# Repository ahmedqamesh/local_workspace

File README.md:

# MyWorkSpace includes a set of libraries and functions for analysis and plotting.
#

# Links
Geant4 :http://geant4.cern.ch/support/download.shtml
Attenuation Data: http://henke.lbl.gov/optical_constants/
http://physics.nist.gov/PhysRefData/XrayMassCoef/tab3.html (only mass absorption coeff Low range)
http://physics.nist.gov/cgi-bin/Xcom/xcom3_1
http://physics.nist.gov/PhysRefData/Xcom/html/xcom1.html  (mass abs coeff  with photoeffekt, compton usw..)	
https://physics.nist.gov/PhysRefData/XrayTrans/Html/search.html			 (X-ray transition energies by element(s), transition(s), and/or energy/wavelength range. )  
# Need to install 
pip install lmfit

# Geant4 installation
wget http://geant4.cern.ch/support/source/geant4.10.01.p01.tar.gz
cmake -DGEANT4_USE_GDML=ON -DGEANT4_INSTALL_DATA=ON -DGEANT4_USE_G3TOG4=ON -DGEANT4_USE_OPENGL_X11=ON -DCMAKE_INSTALL_PREFIX=/home/silab62/HEP/geant4.10.01-install -DGEANT4_BUILD_MULTITHREADED=ON -DGEANT4_USE_QT=ON -DCLHEP_ROOT_DIR=/home/silab62/HEP/Tools/clhep/install ../geant4.10.01.p01
make -j
make install
source /home/silab62/HEP/geant4-install/bin/geant4.sh

# CLHEP installation  
mkdir Tools 
mkdir build install source
cd /home/silab62/HEP/Tools/clhep/build/
mkdir clhep-2.1.3.1
cd clhep-2.1.3.1
cmake ../../source/clhep/
ccmake .
#change CMAKE_INSTALL_PREFIX to /home/silab62/HEP/Tools/clhep/install/
make 
make install

# Root installation 
# First Some libraries:
sudo apt  install cmake
sudo apt-get install git dpkg-dev make g++ gcc binutils libx11-dev libxpm-dev libxft-dev libxext-dev 
sudo apt-get install build-essential git subversion
sudo apt-get install gfortran libssl-dev libpcre3-dev xlibmesa-glu-dev libglew1.5-dev libftgl-dev libmysqlclient-dev libfftw3-dev 
sudo apt-get install libcfitsio-dev graphviz-dev libavahi-compat-libdnssd-dev libldap2-dev python-dev libxml2-dev libkrb5-dev libgsl0-dev libqt4-dev ccache
#Install font packages:
sudo apt-get install xfsprogs #(xfs xfstt)
sudo apt-get install t1-xfree86-nonfree ttf-xfree86-nonfree ttf-xfree86-nonfree-syriac xfonts-75dpi xfonts-100dpi
#Download root itself
Go to https://root.cern.ch/content/release-61804
or 
The entire ROOT source can be obtained from our public Git repository:
git clone http://github.com/root-project/root.git
#The release specific tag can be obtained using:
cd root
git checkout -b v6-18-04 v6-18-04
## Building
Make a directory for building
    $ mkdir build
    $ cd build

Run cmake and make

    $ cmake ../root
    $ make -j8
    $ sudo make install

Setup and run ROOT
    $ source bin/thisroot.sh
    $ root
    
nano ~/.bashrc
#Add the line
source ~/bin/thisroot.sh #/home/qamesh/Installations/root_installer/Source/build/bin/thisroot.sh
export PATH=$ROOTSYS/bin:$PATH
export LD_LIBRARY_PATH=$ROOTSYS/lib:$LD_LIBRARY_PATH   

Add the following in Eclipse
Go to Preferences → C/C++ → Build → Environment.
Add $ROOTSYS variable and its value.
Add $PATH variable. Eclipse needs this path because it will run gdb and our Makefile, which involves executing root-config and rootcling.
Add $DYLD_LIBRARY_PATH on macOS or $LD_LIBRARY_PATH on Linux. When running the project Eclipse needs to know where ROOT’s shared libraries are located.

these two you have to set

the /home/patrick/root/lib has to be also in the libraries
you have to go to PyDeV -> Interpreters -> python interpreter
and there you have to set /home/patrick/root/lib in libraries
and LD_LIBRARY_PATH & ROOTSYS in environment

./configure --all --prefix=/home/silab62/HEP/Tools/root6/install
https://root-forum.cern.ch/t/using-root-gui-in-eclipse/30581

#For Ubuntu 14.04 run: sudo mkdir /usr/include/freetype && sudo cp /usr/include/freetype2/freetype.h /usr/include/freetype/freetype.h
To unistall 
sudo apt-get remove root-system-bin
sudo apt-get remove --auto-remove root-system-bin

# Install wine to run windows applications on Ubuntu
sudo apt install wine64
sudo apt install wine-development
sudo apt install wine-stable

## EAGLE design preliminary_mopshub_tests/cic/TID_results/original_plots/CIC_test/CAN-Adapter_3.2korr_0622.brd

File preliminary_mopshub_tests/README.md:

# Preliminary tests
The testing and validation of the MOPS-Hub includes strict assessments of its hardware components. This scripts involved in this repo aims to ensure the reliability,
functionality, and performance of the MOPS-Hub crate across various scenarios. 
An Arduino-based setup was built to test the modules under controlled conditions.

## List of scripts 
### Test Files
1. **test_can_interface_card.py**: Runs automated tests on the CAN Interface Card (CIC) to ensure correct operation. Data is collected continuously over an extended period using the Arduino-based setup.
2. **test_power_card.py**: Runs automated tests to validate the PP3-power card’s performance and functionality.
- Data is collected continuously over an extended period using the Arduino-based setup. 
- The script control over the connected power supply during operation.
3. **test_power_supply.py** : Controls the supply power during operation [Used during the Proton Campaign].

### Analysis Files
1. **analyze_cic_v2_results.py**: Processes and analyzes data from CAN Interface Card (CIC) tests including:
	- Total Ionizing Dose (TID).
	- Neutron Fluence.
	- Magnetic Field.
2. **analyze_cic_configurations_test.py**: to analyze the data of the VCAN voltages on the CAN Interface Card (CIC) under different Configurations.
3. **analyze_powersupply_results.py**: Analyzes the performance of the power supply to reflect current and voltage behavior of the connected DUT (Device Under Test).
4. **analyze_powercard_results.py**: Processes and analyzes data from PP3-power card tests including: 
	- Total Ionizing Dose (TID).
	- Neutron Fluence.
	- Magnetic Field.
5. **analyze_magnetic_field_results.py**: Creat a magnetic field map for the Lab setup.<br>

**Note**: Data from each test is saved in the directory: `$PROJ_HOME/preliminary_tests/output_dir/`

# Documentation
- Construction of MOPS-Hub document: [AT2-IP-EP-0021](https://edms.cern.ch/document/2600650/1).
- QA/QC of MOPS-Hub document: [AT2-IP-QA-0053](https://edms.cern.ch/document/2600650/1).

# Contributing and Contact Information:
We welcome contributions from the community please contact : 
- Felix Nitz : `fnitz@uni-wuppertal.de`.
- Ahmed Qamesh `ahmed.qamesh@cern.ch`.

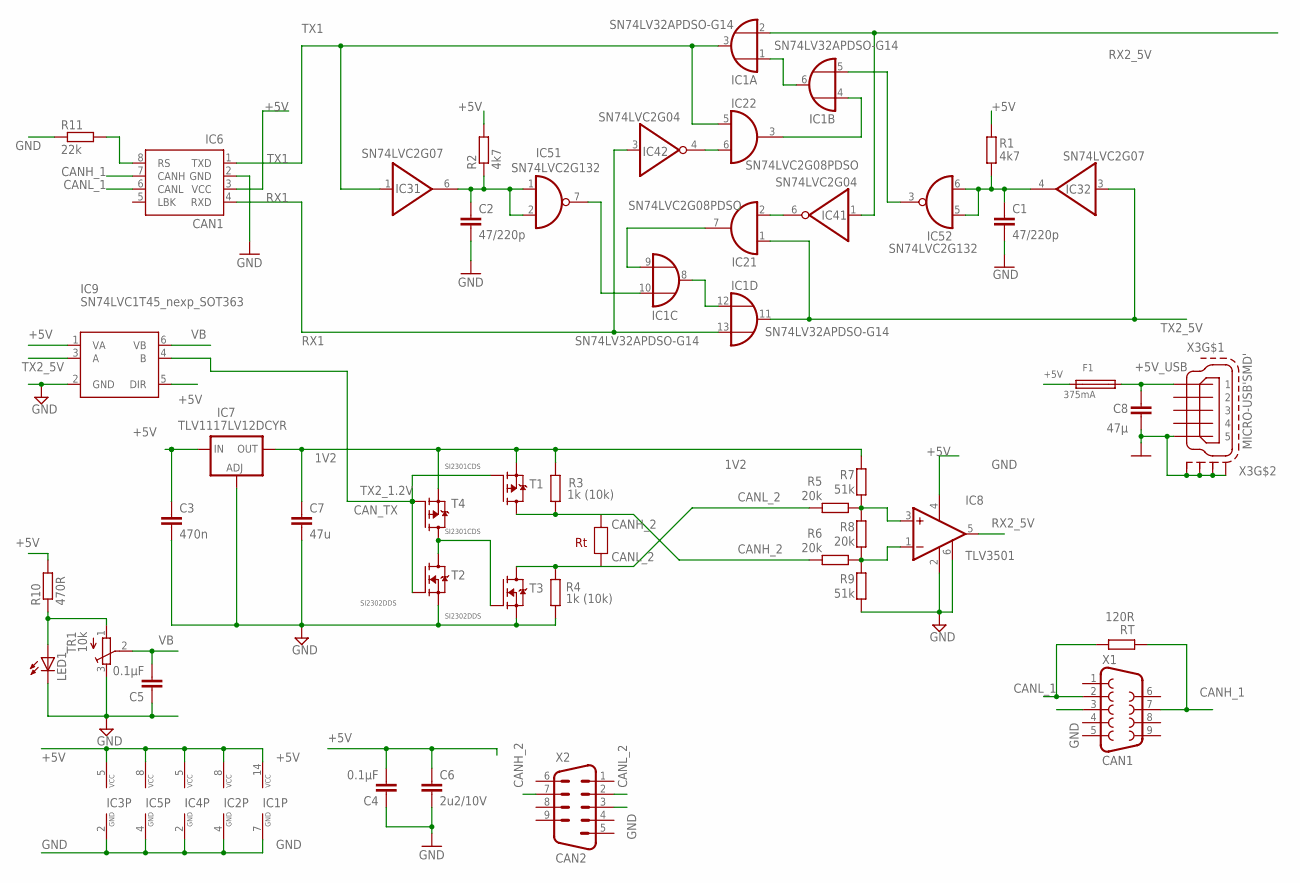
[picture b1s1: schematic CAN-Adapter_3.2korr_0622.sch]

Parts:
C1, C2: 47/220p; C0603
C3: 470n; C1206S
C4, C5: 0.1µF; C0805
C6: 2u2/10V; C0805
C7: 47u; C1206K
C8: 47µ; C1206K
F1: 375mA; 1206
IC1: SN74LV32APDSO-G14; PW_R-PDSO-G14
IC2: SN74LVC2G08PDSO; R-PDSO-G08_DCT
IC3: SN74LVC2G07; R-PDSO-G06
IC4: SN74LVC2G04; R-PDSO-G06
IC5: SN74LVC2G132; S-PDSO-G08_DCU
IC6: CAN1; SO-08
IC7: TLV1117LV12DCYR; SOT223
IC8: TLV3501; SOT23-6
IC9: SN74LVC1T45_nexp_SOT363; SOT363
LED1: LED3MM
R1, R2: 4k7; R0603
R3, R4: 1k (10k); R0603
R5, R6, R8: 20k; R0603
R7, R9: 51k; R0603
R10: 470R; R0603
R11: 22k; R0603
RT: 120R; R0603
T1, T4: SI2301CDS; SOT23
T2, T3: SI2302DDS; SOT23
TR1: 10k; TC33X-2
X1: CAN1; F09D
X2: CAN2; M09D
X3: MICRO-USB'SMD'; MICRO-USB_SMD

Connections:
1V2: C7.1, IC7.4 (OUT), R3.2, R7.1, T1.2 (S), T4.2 (S)
+5V: C3.1, C4.2, C6.1, F1.P$1 (1), IC1.14 (VCC), IC2.8 (VCC), IC3.5 (VCC), IC4.5 (VCC), IC5.8 (VCC), IC6.3 (VCC), IC7.3 (IN), IC8.4 (V+), IC9.1 (VA), IC9.5 (DIR), R1.2, R2.2, R10.2
+5V_USB: C8.1, F1.P$2 (2), X3.P$1 (1)
CANH_1: IC6.7 (CANH), RT.1, X1.7
CANH_2: R3.1, R6.1, T1.3 (D), X2.7
CANL_1: IC6.6 (CANL), RT.2, X1.2
CANL_2: R4.2, R5.1, T3.3 (D), X2.2
GND: C1.2, C2.2, C3.2, C4.1, C5.1, C6.2, C7.2, C8.2, IC1.7 (GND), IC2.4 (GND), IC3.2 (GND), IC4.2 (GND), IC5.4 (GND), IC6.2 (GND), IC7.1 (ADJ), IC8.2 (V-), IC8.6 (SHDN), IC9.2 (GND), LED1.K (C), R4.1, R9.2, R11.1, T2.2 (S), T3.2 (S), TR1.3 (E), X1.3, X2.3, X3.P$5 (5), X3.P$6 (S1), X3.P$7 (S2), X3.P$8 (S3), X3.P$9 (S4)
IC1,6: IC1.1 (I0), IC1.6 (O)
IC1,8: IC1.8 (O), IC1.12 (I0)
IC2,3: IC1.4 (I0), IC2.3 (Y)
IC2,7: IC1.9 (I0), IC2.7 (Y)
IC3,4: C1.1, IC3.4 (Y), IC5.5 (A), IC5.6 (B), R1.1
IC3,6: C2.1, IC3.6 (Y), IC5.1 (A), IC5.2 (B), R2.1
IC4,4: IC2.6 (B), IC4.4 (Y)
IC4,6: IC2.2 (B), IC4.6 (Y)
IC5,3: IC1.5 (I1), IC5.3 (Y)
IC5,7: IC1.10 (I1), IC5.7 (Y)
unnamed: T2.3 (D), T3.1 (G), T4.3 (D)
unnamed: LED1.A, R10.1, TR1.1 (A)
unnamed: IC6.8 (RS), R11.2
unnamed: IC8.3 (+IN), R5.2, R7.2, R8.1
unnamed: IC8.1 (-IN), R6.2, R8.2, R9.1
RX1: IC1.13 (I1), IC4.3 (A), IC6.4 (RXD)
RX2_5V: IC1.2 (I1), IC4.1 (A), IC8.5 (OUT)
TX1: IC1.3 (O), IC2.5 (A), IC3.1 (A), IC6.1 (TXD)
TX2_1.2V: IC9.4 (B), T1.1 (G), T2.1 (G), T4.1 (G)
TX2_5V: IC1.11 (O), IC2.1 (A), IC3.3 (A), IC9.3 (A)
VB: C5.2, IC9.6 (VB), TR1.2 (S)

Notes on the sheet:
CAN_TX
SN74LVC2G08PDSO

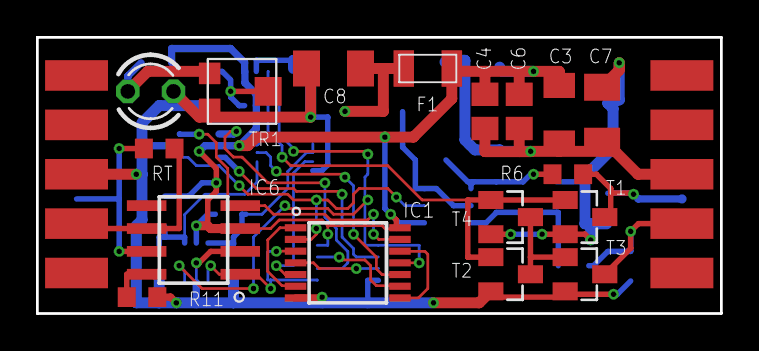
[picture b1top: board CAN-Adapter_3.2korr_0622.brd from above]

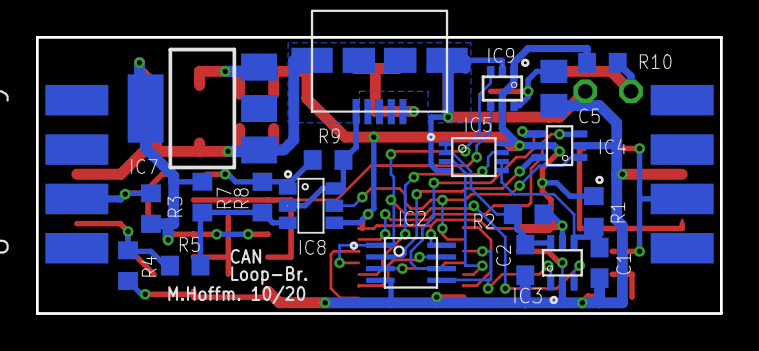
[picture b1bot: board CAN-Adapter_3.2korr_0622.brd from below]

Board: 2 copper layers, 38.0 x 15.3 mm, 39 parts (20 on the bottom side), 29 nets.

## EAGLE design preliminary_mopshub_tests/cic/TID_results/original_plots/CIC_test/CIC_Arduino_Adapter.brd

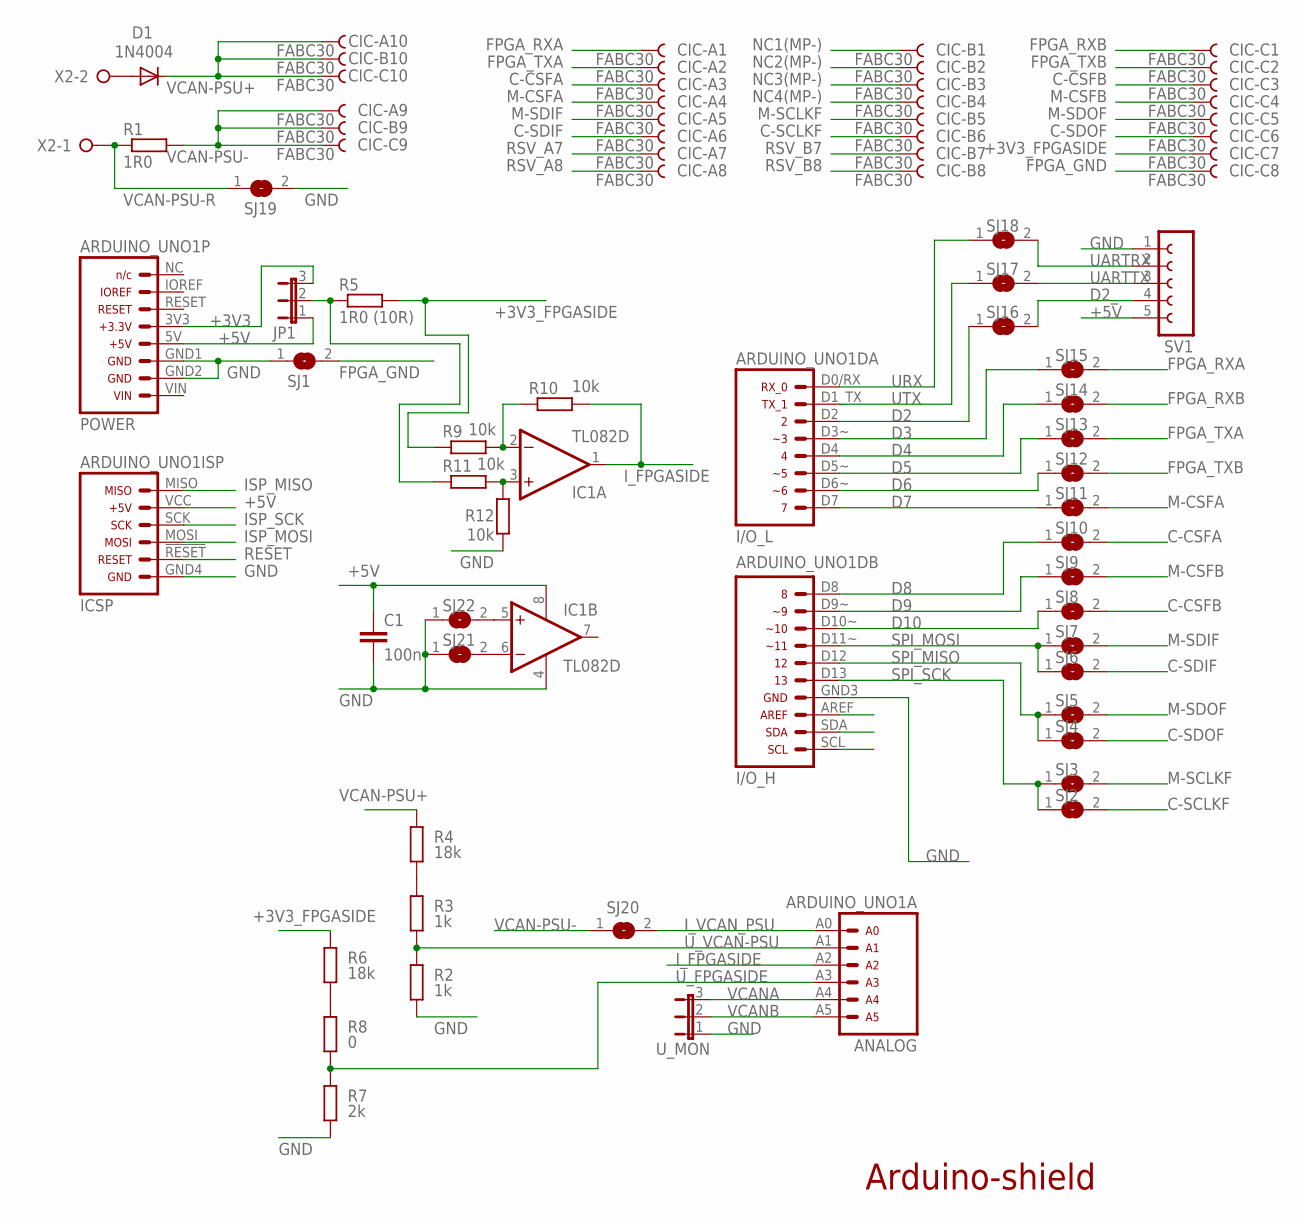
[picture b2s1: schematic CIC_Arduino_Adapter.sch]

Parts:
ARDUINO_UNO1: SHELL_UNO1; SHELL_UNO_1
C1: 100n; C0805
CIC: FABC30
D1: 1N4004; DO41-10
IC1: TL082D; SO08
JP1: JP2E; JP2
R1: 1R0; 0207/2V
R2, R3: 1k; 0207/2V
R4, R6: 18k; 0207/2V
R5: 1R0 (10R); 0207/2V
R7: 2k; 0207/2V
R8: 0; 0207/2V
R9, R10, R11, R12: 10k; R0805
SJ1, SJ2, SJ3, SJ4, SJ5, SJ6, SJ7, SJ8, SJ9, SJ10, SJ11, SJ12, SJ13, SJ14, SJ15, SJ16, SJ17, SJ18, SJ19, SJ20, SJ21, SJ22: SJ
SV1: FE05-1
U_MON: JP2E; JP2
X2: W237-2N

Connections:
+3V3: ARDUINO_UNO1.3V3 (4), JP1.3
+3V3_FPGASIDE: CIC.C7, R5.2, R6.2, R9.1
+5V: ARDUINO_UNO1.5V (5), ARDUINO_UNO1.VCC (2), C1.1, IC1.8 (V+), JP1.1, SV1.5
C-CSFA: CIC.A3, SJ10.2
C-CSFB: CIC.C3, SJ8.2
C-SCLKF: CIC.B6, SJ2.2
C-SDIF: CIC.A6, SJ6.2
C-SDOF: CIC.C6, SJ4.2
D2: ARDUINO_UNO1.D2 (3), SJ16.1
D2_: SJ16.2, SV1.4
D3: ARDUINO_UNO1.D3~ (4), SJ15.1
D4: ARDUINO_UNO1.D4 (5), SJ14.1
D5: ARDUINO_UNO1.D5~ (6), SJ13.1
D6: ARDUINO_UNO1.D6~ (7), SJ12.1
D7: ARDUINO_UNO1.D7 (8), SJ11.1
D8: ARDUINO_UNO1.D8 (1), SJ10.1
D9: ARDUINO_UNO1.D9~ (2), SJ9.1
D10: ARDUINO_UNO1.D10~ (3), SJ8.1
FPGA_GND: CIC.C8, SJ1.2
FPGA_RXA: CIC.A1, SJ15.2
FPGA_RXB: CIC.C1, SJ14.2
FPGA_TXA: CIC.A2, SJ13.2
FPGA_TXB: CIC.C2, SJ12.2
GND: ARDUINO_UNO1.GND1 (6), ARDUINO_UNO1.GND2 (7), ARDUINO_UNO1.GND3 (7), ARDUINO_UNO1.GND4 (6), C1.2, IC1.4 (V-), R2.1, R7.1, R12.1, SJ1.1, SJ19.2, SJ21.1, SJ22.1, SV1.1, U_MON.1
ISP_MISO: ARDUINO_UNO1.MISO (1)
ISP_MOSI: ARDUINO_UNO1.MOSI (4)
ISP_SCK: ARDUINO_UNO1.SCK (3)
I_FPGASIDE: ARDUINO_UNO1.A2 (3), IC1.1 (OUT), R10.2
I_VCAN_PSU: ARDUINO_UNO1.A0 (1), SJ20.2
M-CSFA: CIC.A4, SJ11.2
M-CSFB: CIC.C4, SJ9.2
M-SCLKF: CIC.B5, SJ3.2
M-SDIF: CIC.A5, SJ7.2
M-SDOF: CIC.C5, SJ5.2
unnamed: IC1.2 (-IN), R9.2, R10.1
unnamed: JP1.2, R5.1, R11.1
unnamed: R6.1, R8.2
unnamed: IC1.3 (+IN), R11.2, R12.2
unnamed: IC1.6 (-IN), SJ21.2
unnamed: IC1.5 (+IN), SJ22.2
unnamed: R3.2, R4.1
unnamed: D1.A, X2.2
NC1(MP-): CIC.B1
NC2(MP-): CIC.B2
NC3(MP-): CIC.B3
NC4(MP-): CIC.B4
RESET: ARDUINO_UNO1.!RESET (5)
RSV_A7: CIC.A7
RSV_A8: CIC.A8
RSV_B7: CIC.B7
RSV_B8: CIC.B8
SPI_MISO: ARDUINO_UNO1.D12 (5), SJ4.1, SJ5.1
SPI_MOSI: ARDUINO_UNO1.D11~ (4), SJ6.1, SJ7.1
SPI_SCK: ARDUINO_UNO1.D13 (6), SJ2.1, SJ3.1
UARTRX: SJ18.2, SV1.2
UARTTX: SJ17.2, SV1.3
URX: ARDUINO_UNO1.D0/RX (1), SJ18.1
UTX: ARDUINO_UNO1.D1_TX (2), SJ17.1
U_FPGASIDE: ARDUINO_UNO1.A3 (4), R7.2, R8.1
U_VCAN-PSU: ARDUINO_UNO1.A1 (2), R2.2, R3.1
VCAN-PSU+: CIC.A10, CIC.B10, CIC.C10, D1.C, R4.2
VCAN-PSU-: CIC.A9, CIC.B9, CIC.C9, R1.2, SJ20.1
VCAN-PSU-R: R1.1, SJ19.1, X2.1
VCANA: ARDUINO_UNO1.A4 (5), U_MON.3
VCANB: ARDUINO_UNO1.A5 (6), U_MON.2

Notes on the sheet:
Arduino-shield

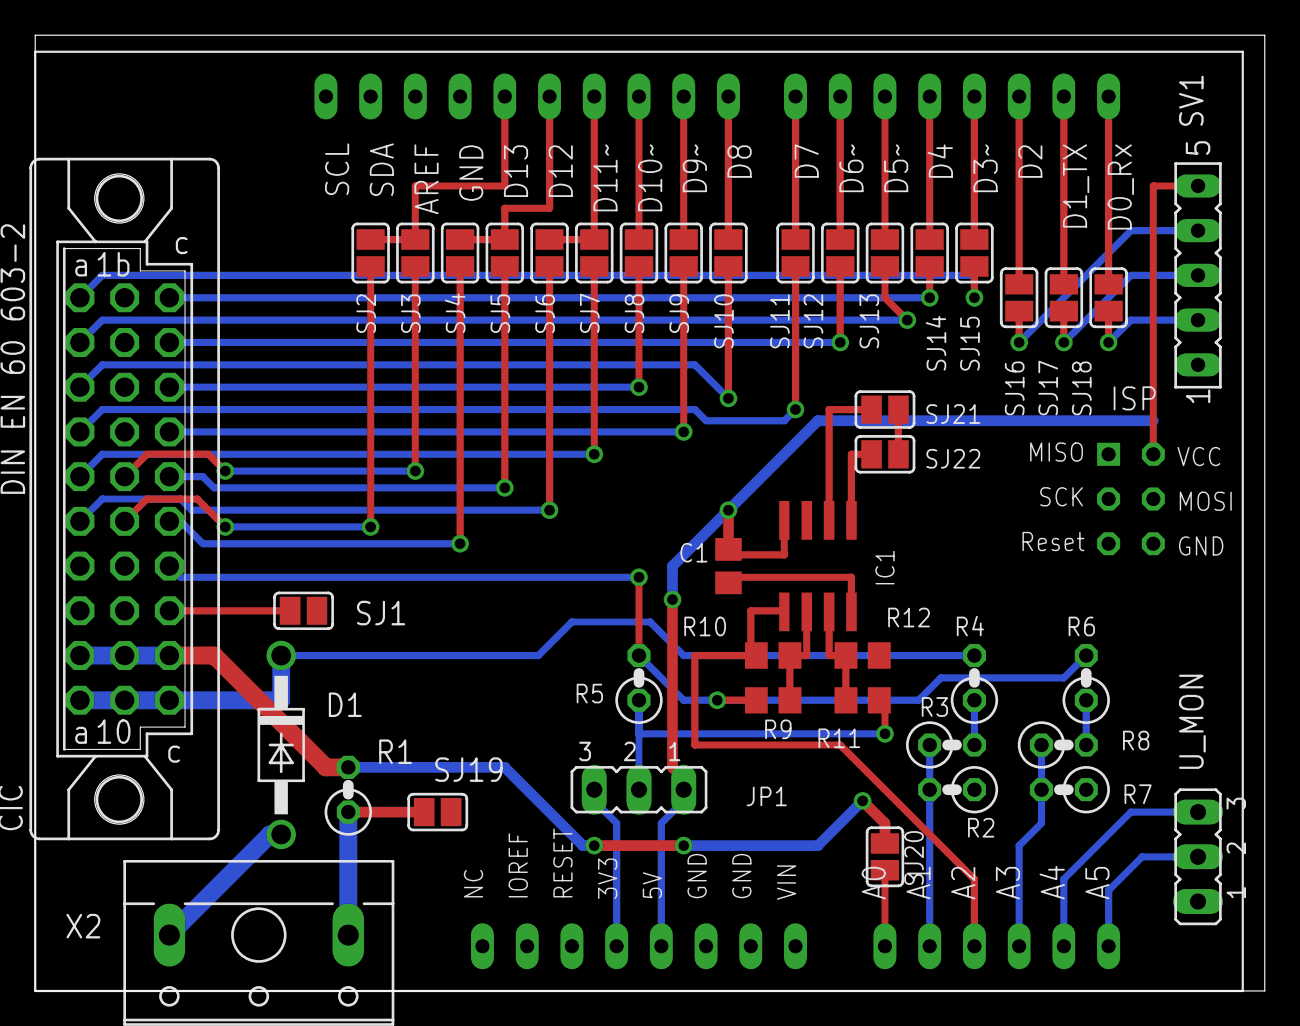
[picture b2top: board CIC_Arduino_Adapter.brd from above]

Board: 2 copper layers, 69.8 x 54.3 mm, 43 parts (0 on the bottom side), 53 nets.

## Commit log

2018-10-29 To get the calibration curves for each current
2018-10-29 Create Trial
2018-10-29 Create Bonn
2018-10-29 Create 0
2018-10-29 Create 3cm
2018-10-29 Create 5cm
2018-10-29 Rename 5cm to 8cm
2018-10-29 Create Dose_Depth
2018-10-29 Create 30KV
2018-10-29 Create 40KV
2018-10-29 Create 30mA
2018-10-29 Create 8cm
2018-10-29 uploaded data files
2018-10-29 Add some output directories
2018-11-05 Dose-Depth for data without filter
2018-11-05 Add Simulation
2018-11-06 Some extra plots for Depth vs Dose
2018-11-07 Lead Attenuation
2018-11-08 Changing the style
2018-11-08 Add attenuation plots
2018-11-08 Extra function for attenuation
2018-11-10 Geant4 simulation
2018-11-10 clean up
2018-11-10 Geant4 Simulation Activated
2018-11-11 Clean
2018-11-11 New Features for Geant4
2018-11-12 Adding X ray Spectrum plotting
2018-11-13 Enhancement
2018-11-17 ENH: Geant4 update with Callorimeter
2018-11-17 Adding Manuals
2018-11-23 Add some Feature to Geant4
2019-01-03 ENH: Finally , the beam spot scan is ready
2019-01-03 Intime beam spot plotting
2019-01-10 ENH: beam profile 3 cm
2019-01-15 beam profile
2019-02-12 Final
2019-10-28 Update: Separate library for analysis
2019-10-28 Edit README
2019-10-29 Add logging functions
2019-10-31 Add Root Libraries
2019-11-21 OPCUA
2019-11-21 New image
2019-11-21 New images eclipse
2019-11-21 Python images
2019-11-21 new image OPCUA
2019-11-21 anagate Wiki images
2019-11-21 linux
2019-11-22 OPCUA pic
2019-11-22 Last Push from Ubuntu
2020-01-10 Trial 2020
2020-04-03 photos
2020-04-07 rise time
2020-09-25 DC/DC converters
2023-05-02 adding ignore
2023-05-02 adding
2023-05-02 adding2
2025-01-10 Final submission before handing over
2025-01-13 last
